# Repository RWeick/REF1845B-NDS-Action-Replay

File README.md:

# REF1845B-NDS-Action-Replay
The full schematic, flash dump, and gerbers for the Nintendo DS Action Replay by Datel. The apparent micro SD card slot footprint on the back of the PCB is not connected properly. It is possibly a JTAG connection.

PCB Thickness: 0.8 mm

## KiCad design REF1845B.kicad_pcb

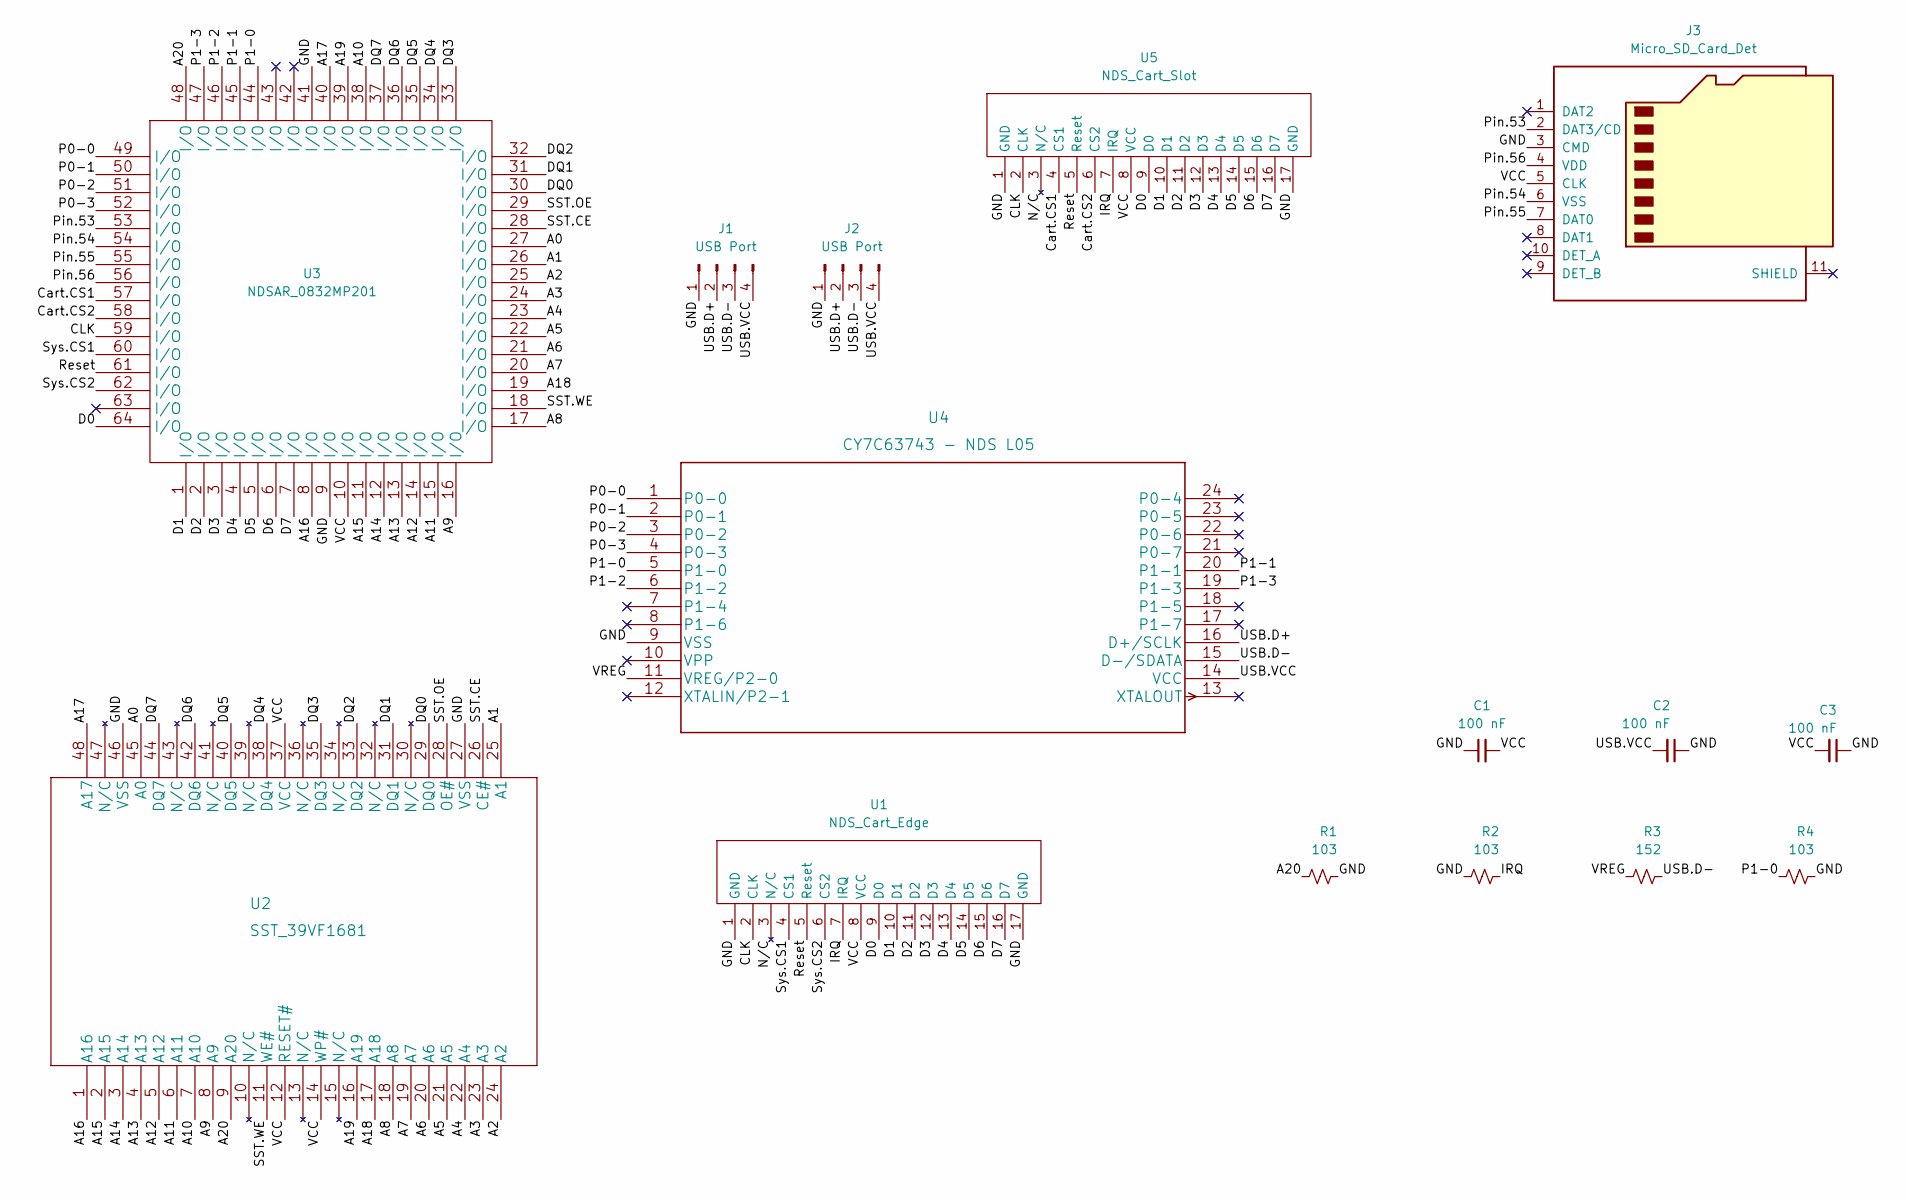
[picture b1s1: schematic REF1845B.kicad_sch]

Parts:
C1, C2, C3: 100 nF; Little SMD
J1, J2: USB Port; USB Adapter
J3: Micro_SD_Card_Det; Micro SD Card
R1, R2, R4: 103; Little SMD
R3: 152; Little SMD
U1: NDS_Cart_Edge; Edge Connector
U2: SST_39VF1681; SOP50P2000X120-48N
U3: NDSAR_0832MP201; 64 pin FPGA DS AR
U4: CY7C63743 - NDS L05; CY7C63743 24 lead quarter size
U5: NDS_Cart_Slot; DS Slot

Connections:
/A0: U2.45 (A0), U3.27 (I/O)
/A1: U2.25 (A1), U3.26 (I/O)
/A2: U2.24 (A2), U3.25 (I/O)
/A3: U2.23 (A3), U3.24 (I/O)
/A4: U2.22 (A4), U3.23 (I/O)
/A5: U2.21 (A5), U3.22 (I/O)
/A6: U2.20 (A6), U3.21 (I/O)
/A7: U2.19 (A7), U3.20 (I/O)
/A8: U2.18 (A8), U3.17 (I/O)
/A9: U2.8 (A9), U3.16 (I/O)
/A10: U2.7 (A10), U3.38 (I/O)
/A11: U2.6 (A11), U3.15 (I/O)
/A12: U2.5 (A12), U3.14 (I/O)
/A13: U2.4 (A13), U3.13 (I/O)
/A14: U2.3 (A14), U3.12 (I/O)
/A15: U2.2 (A15), U3.11 (I/O)
/A16: U2.1 (A16), U3.8 (I/O)
/A17: U2.48 (A17), U3.40 (I/O)
/A18: U2.17 (A18), U3.19 (I/O)
/A19: U2.16 (A19), U3.39 (I/O)
/A20: R1.2, U2.9 (A20), U3.48 (I/O)
/CLK: U1.2 (CLK), U3.59 (I/O), U5.2 (CLK)
/Cart.CS1: U3.57 (I/O), U5.4 (CS1)
/Cart.CS2: U3.58 (I/O), U5.6 (CS2)
/D0: U1.9 (D0), U3.64 (I/O), U5.9 (D0)
/D1: U1.10 (D1), U3.1 (I/O), U5.10 (D1)
/D2: U1.11 (D2), U3.2 (I/O), U5.11 (D2)
/D3: U1.12 (D3), U3.3 (I/O), U5.12 (D3)
/D4: U1.13 (D4), U3.4 (I/O), U5.13 (D4)
/D5: U1.14 (D5), U3.5 (I/O), U5.14 (D5)
/D6: U1.15 (D6), U3.6 (I/O), U5.15 (D6)
/D7: U1.16 (D7), U3.7 (I/O), U5.16 (D7)
/DQ0: U2.29 (DQ0), U3.30 (I/O)
/DQ1: U2.31 (DQ1), U3.31 (I/O)
/DQ2: U2.33 (DQ2), U3.32 (I/O)
/DQ3: U2.35 (DQ3), U3.33 (I/O)
/DQ4: U2.38 (DQ4), U3.34 (I/O)
/DQ5: U2.40 (DQ5), U3.35 (I/O)
/DQ6: U2.42 (DQ6), U3.36 (I/O)
/DQ7: U2.44 (DQ7), U3.37 (I/O)
/GND: C1.1, C2.2, C3.2, J1.1, J2.1, J3.3 (CMD), R1.1, R2.2, R4.1, U1.1 (GND), U1.17 (GND), U2.27 (VSS), U2.46 (VSS), U3.9 (I/O), U3.41 (I/O), U4.9 (VSS), U5.1 (GND), U5.17 (GND)
/IRQ: R2.1, U1.7 (IRQ), U5.7 (IRQ)
/P0-0: U3.49 (I/O), U4.1 (P0-0)
/P0-1: U3.50 (I/O), U4.2 (P0-1)
/P0-2: U3.51 (I/O), U4.3 (P0-2)
/P0-3: U3.52 (I/O), U4.4 (P0-3)
/P1-0: R4.2, U3.44 (I/O), U4.5 (P1-0)
/P1-1: U3.45 (I/O), U4.20 (P1-1)
/P1-2: U3.46 (I/O), U4.6 (P1-2)
/P1-3: U3.47 (I/O), U4.19 (P1-3)
/Pin.53: J3.2 (DAT3/CD), U3.53 (I/O)
/Pin.54: J3.6 (VSS), U3.54 (I/O)
/Pin.55: J3.7 (DAT0), U3.55 (I/O)
/Pin.56: J3.4 (VDD), U3.56 (I/O)
/Reset: U1.5 (Reset), U3.61 (I/O), U5.5 (Reset)
/SST.CE: U2.26 (CE#), U3.28 (I/O)
/SST.OE: U2.28 (OE#), U3.29 (I/O)
/SST.WE: U2.11 (WE#), U3.18 (I/O)
/Sys.CS1: U1.4 (CS1), U3.60 (I/O)
/Sys.CS2: U1.6 (CS2), U3.62 (I/O)
/USB.D+: J1.2, J2.2, U4.16 (D+/SCLK)
/USB.D-: J1.3, J2.3, R3.1, U4.15 (D-/SDATA)
/USB.VCC: C2.1, J1.4, J2.4, U4.14 (VCC)
/VCC: C1.2, C3.1, J3.5 (CLK), U1.8 (VCC), U2.12 (RESET#), U2.14 (WP#), U2.37 (VCC), U3.10 (I/O), U5.8 (VCC)
/VREG: R3.2, U4.11 (VREG/P2-0)

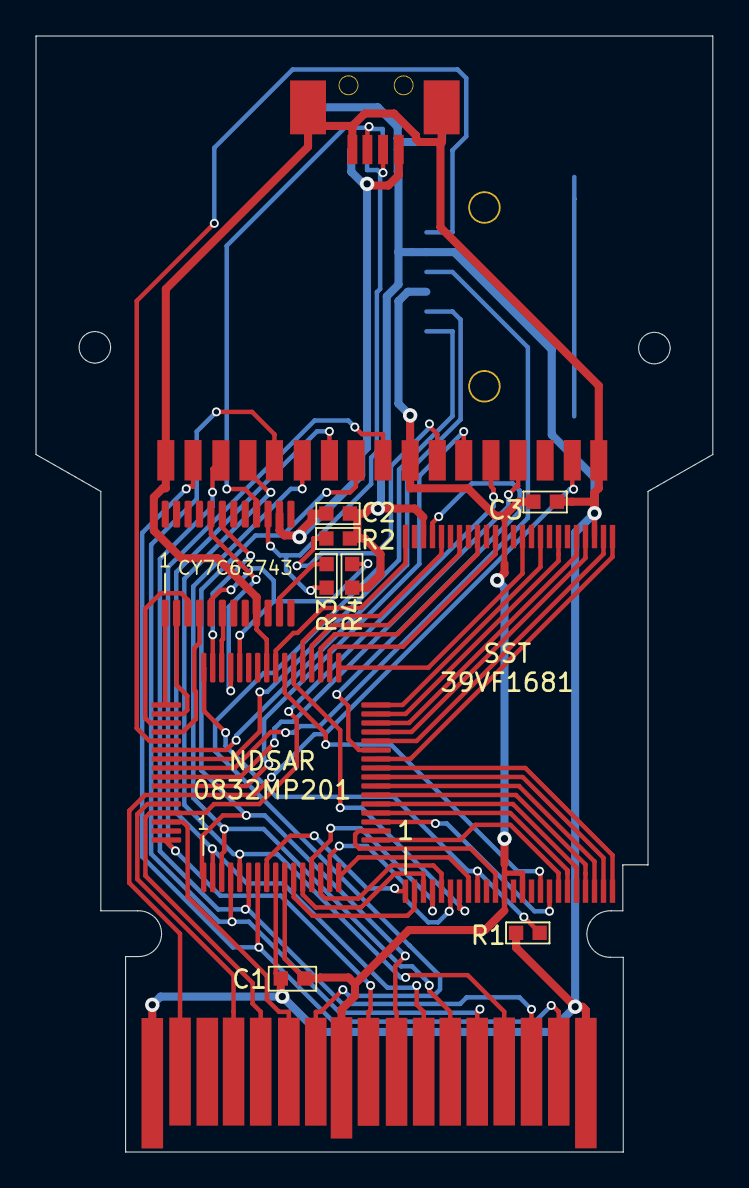
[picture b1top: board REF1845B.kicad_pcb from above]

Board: 2 copper layers, 37.6 x 62.0 mm, 17 parts (1 on the bottom side), 65 nets.

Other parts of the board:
H1, H2: MountingHole_2.1mm
